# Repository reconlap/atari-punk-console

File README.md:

## Synopsis

The source files I used to creating a Atari Punk Console. Mainly covers the creation of a singled sided PCB design that uses two 555 IC timers. If you are wondering what a Atari Punk Console is you can find out by visiting http://www.ataripunkconsole.com/ 

## Motivation

The main motivation was to learn how to layout and produce PCB designs to my specifications,I plan to cut the PCB on my small homemade CNC. Also the Atari Punk Console is a fun little project.

## Contributors

My thanks go to Forrest M. Mims III and for the original design. janw for the design with the added volume control that I based my console on (http://www.instructables.com/id/Voltage-Controlable-Atari-Punk-Console/step2/The-circuit/). 

## License

This source is released under the GNU General Public License (GNU GPLv3).
http://www.gnu.org/licenses/gpl.html

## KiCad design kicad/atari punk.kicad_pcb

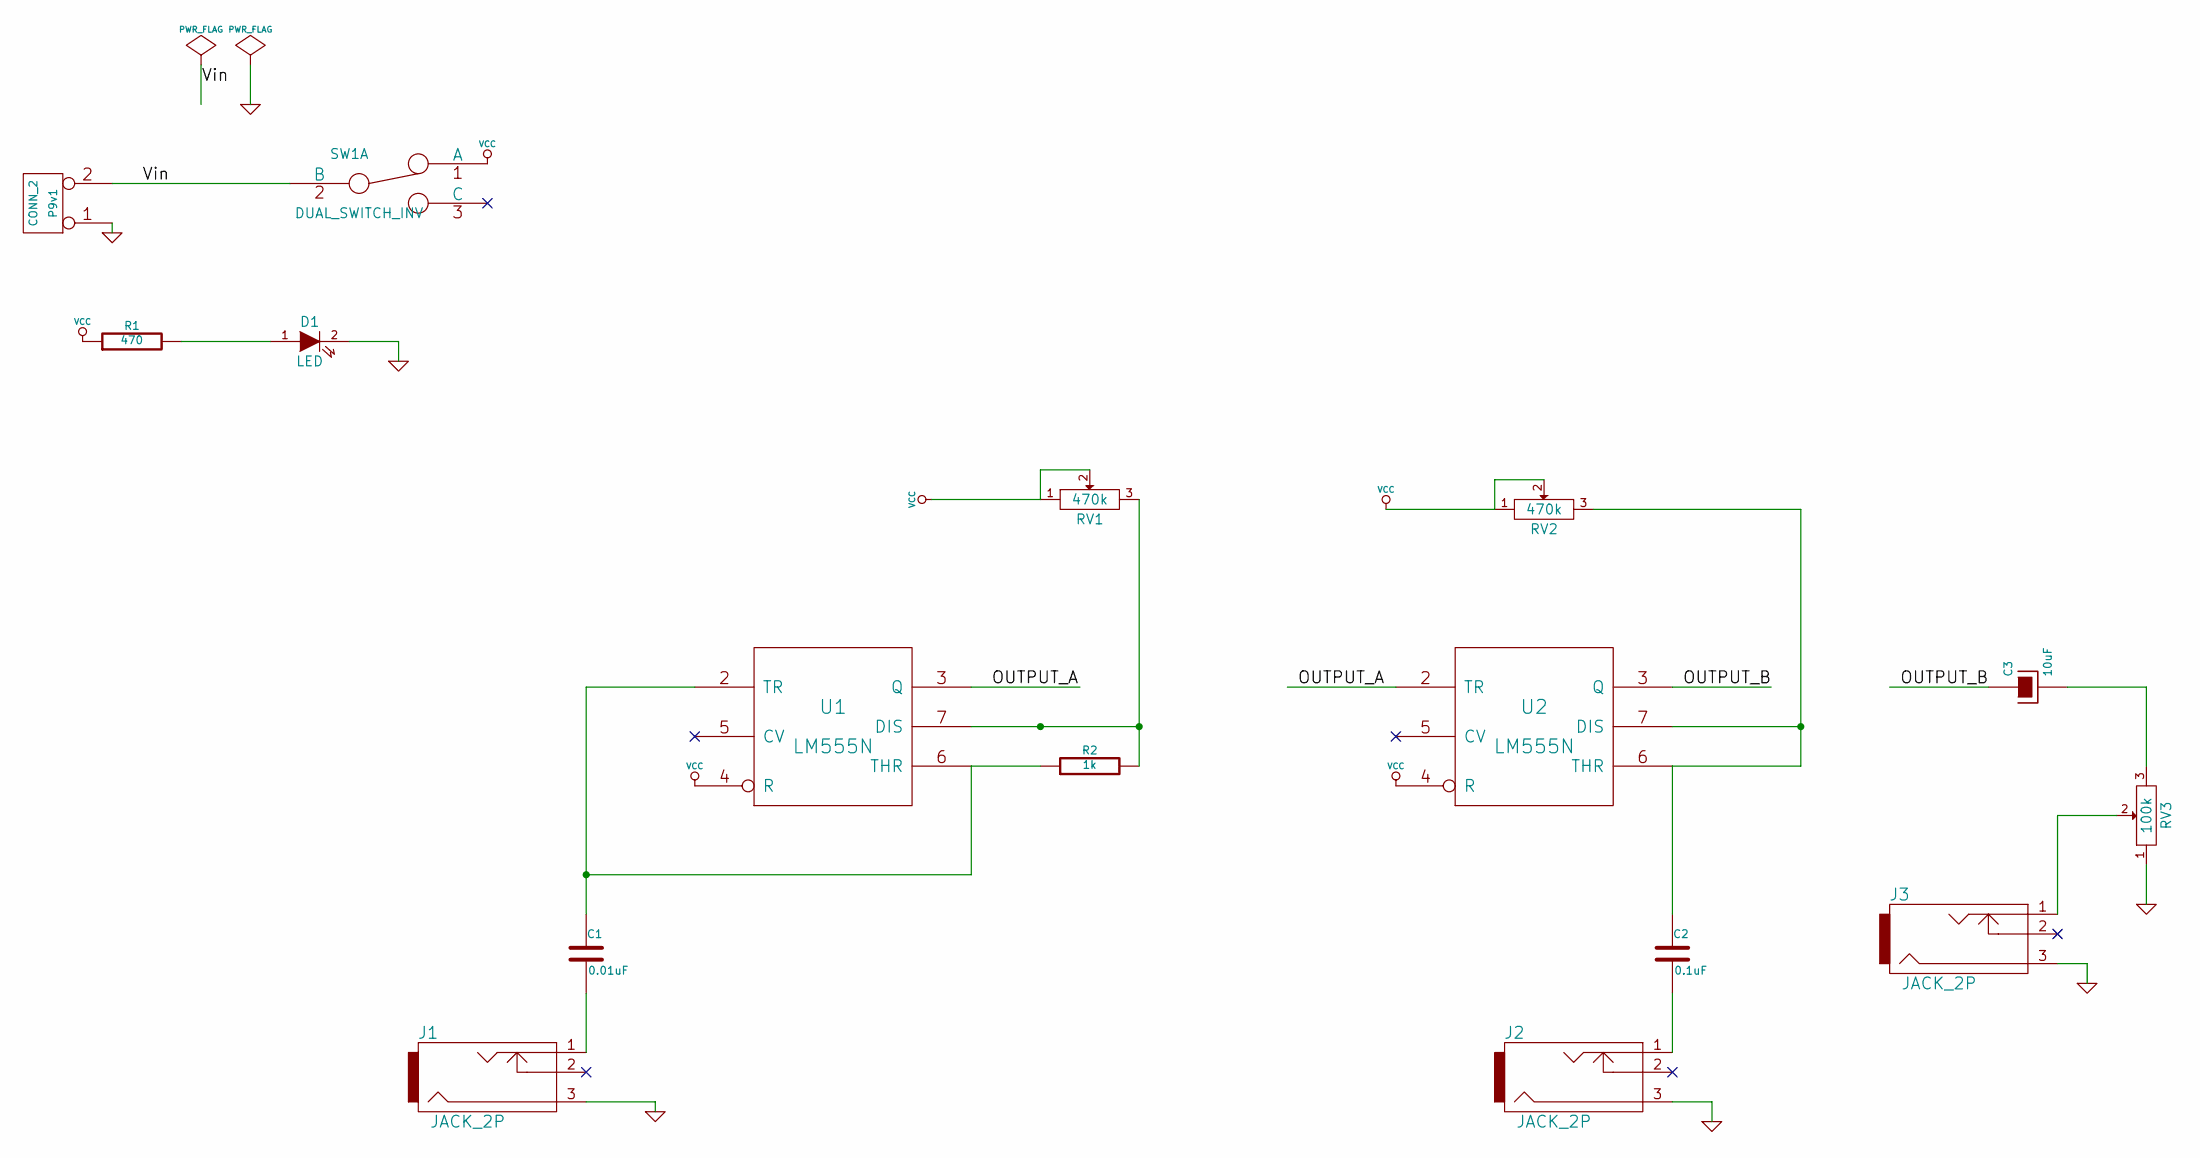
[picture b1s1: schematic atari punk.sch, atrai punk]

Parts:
C1: 0.01uF
C2: 0.1uF
C3: 10uF
D1: LED
J1, J2, J3: JACK_2P
P9v1: CONN_2
R1: 470
R2: 1k
RV1, RV2: 470k
RV3: 100k
SW1: DUAL_SWITCH_INV
U1, U2: LM555N

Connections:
/OUTPUT_A: U1.3 (Q), U2.2 (TR)
/OUTPUT_B: C3.1, U2.3 (Q)
/Vin: P9v1.2 (PM), SW1.2 (B)
GND: D1.2 (K), J1.3, J2.3, J3.3, P9v1.1, RV3.1, U1.1 (GND), U2.1 (GND)
unnamed: R2.2, RV1.3, U1.7 (DIS)
unnamed: C1.1, R2.1, U1.2 (TR), U1.6 (THR)
unnamed: C3.2, RV3.3
unnamed: D1.1 (A), R1.2
unnamed: C2.1, RV2.3, U2.6 (THR), U2.7 (DIS)
unnamed: C2.2, J2.1
unnamed: C1.2, J1.1
unnamed: J3.1, RV3.2
VCC: R1.1, RV1.1, RV1.2, RV2.1, RV2.2, SW1.1 (A), U1.4 (R), U1.8 (VCC), U2.4 (R), U2.8 (VCC)

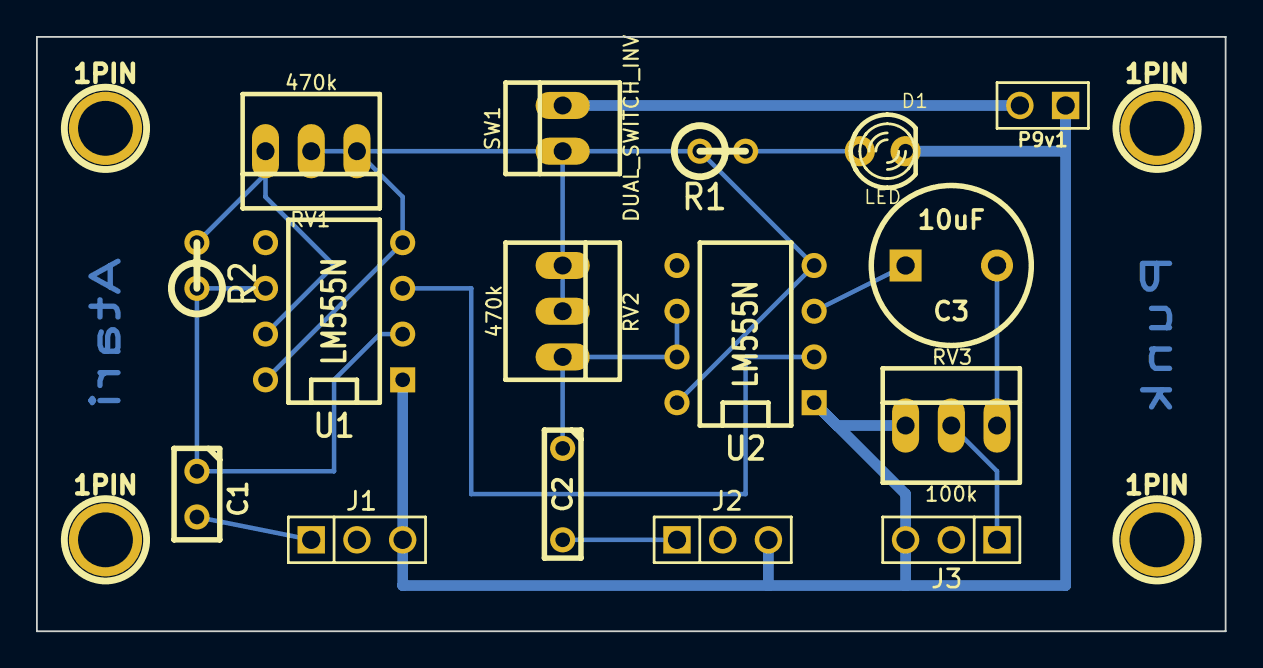
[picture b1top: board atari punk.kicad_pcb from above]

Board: 2 copper layers, 66.0 x 33.0 mm, 20 parts (0 on the bottom side), 13 nets.

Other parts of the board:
1PIN, 1PIN#2, 1PIN#3, 1PIN#4: P***; 1pin

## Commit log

2014-11-29 added Atari Punk Console single sided PCB design v1.
2014-11-29 fixed some spelling mistakes.
2014-11-29 Added missing tracks, made GND and Vin tracks 0.6mm.
2014-11-29 added kicad plot in gerbel format with drill file.
2014-11-29 Fixed a bad track at R2.
2015-02-22 Added first PCB transprancy files.
2015-02-28 Added atari punk pcb tracks stl.
2015-02-28 added pcb tracks blend file.
2015-03-01 Added picture of first try at printing a PCB template.
2015-03-06 renamed atari_punk_tran folder, updated pcb transperancy, added pic of dry film prepared pcb
2015-03-10 added pictures of first etch, moved transfers to different directory.
